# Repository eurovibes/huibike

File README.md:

<!-- SPDX-FileCopyrightText: 2023 Benedikt Spranger <bene@eurovibes.org> -->
<!-- SPDX-License-Identifier: CERN-OHL-S-2.0 -->

# huibike - Bike magnet sensor adaption board

## License rules

huibike is provided under the terms of the CERN-OHL-S license version 2 as
provided in the LICENSES/CERN-OHL-S-2.0 file.

Instead of adding license boilerplates to the individual files, huibike uses
SPDX license identifiers, which are machine parseable and considered legaly
equivalent.

The SPDX license identifier in huibike shall be added at the first possible
line in a file which can contain a comment. This is normally the first line
except for scripts. Scripts require the #!PATH_TO_INTERPRETER tag in the
first line; place the SPDX identifier into the second line.

The SPDX license identifier is added in form of a comment.

## Copyright and License

Copyright Benedikt Spranger 2021.
This source describes Open Hardware and is licensed under the CERNOHL-S v2.
You may redistribute and modify this source and make products using it
under the terms of the CERN-OHL-S v2
(https://ohwr.org/cern ohl s v2.txt ).
This source is distributed WITHOUT ANY EXPRESS OR IMPLIED
WARRANTY, INCLUDING OF MERCHANTABILITY, SATISFACTORY
QUALITY AND FITNESS FOR A PARTICULAR PURPOSE. Please see
the CERN-OHL-S v2 for applicable conditions.
Source location: https://github.com/eurovibes/huibike
As per CERN-OHL-S v2 section 4, should You produce hardware based
on this source, You must where practicable maintain the Source Location
visible on the external case of the huibike or other products you make using
this source.

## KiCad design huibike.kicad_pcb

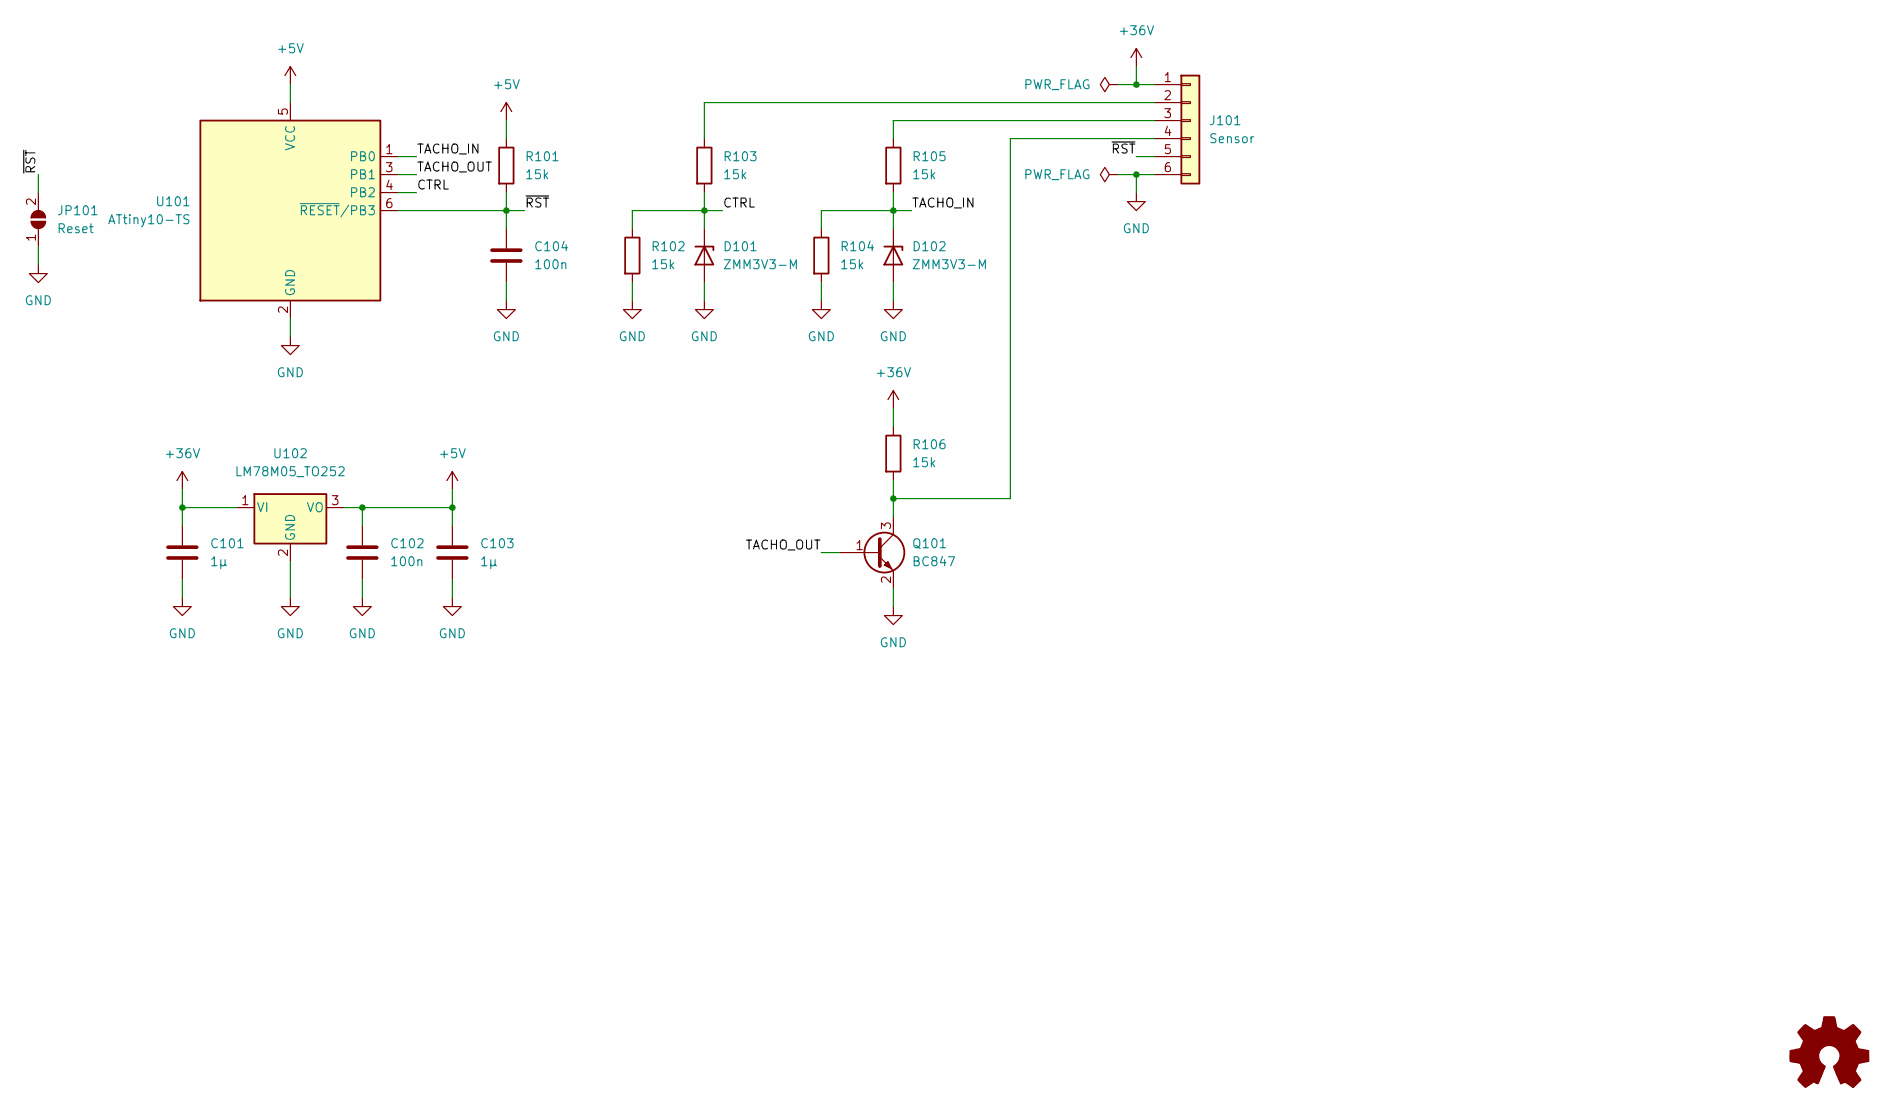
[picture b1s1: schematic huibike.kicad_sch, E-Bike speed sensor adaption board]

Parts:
C101, C103: 1µ; C_0805_2012Metric; LCSC# C28323
C102, C104: 100n; C_0402_1005Metric; LCSC# C1525
D101, D102: ZMM3V3-M; D_MiniMELF; LCSC# C8056
J101: Sensor; PinHeader_1x06_P2.54mm_Vertical
JP101: Reset; SolderJumper-2_P1.3mm_Open_Pad1.0x1.5mm
Q101: BC847; SOT-23; LCSC# C475630
R101, R102, R103, R104, R105, R106: 15k; R_0402_1005Metric; LCSC# C25756
U101: ATtiny10-TS; SOT-23-6; LCSC# C128438
U102: LM78M05_TO252; TO-252-2; LCSC# C58069

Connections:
+5V: C102.1, C103.1, R101.1, U101.5 (VCC), U102.3 (VO)
+36V: C101.1, J101.1, R106.1, U102.1 (VI)
/CTRL: D101.1 (K), R102.1, R103.2, U101.4 (PB2)
/TACHO_IN: D102.1 (K), R104.1, R105.2, U101.1 (PB0)
/TACHO_OUT: Q101.1 (B), U101.3 (PB1)
/~RST: C104.1, J101.5, JP101.2 (B), R101.2, U101.6 (~RESET/PB3)
GND: C101.2, C102.2, C103.2, C104.2, D101.2 (A), D102.2 (A), J101.6, JP101.1 (A), Q101.2 (E), R102.2, R104.2, U101.2 (GND), U102.2 (GND)
unnamed: J101.2, R103.1
unnamed: J101.3, R105.1
unnamed: J101.4, Q101.3 (C), R106.2

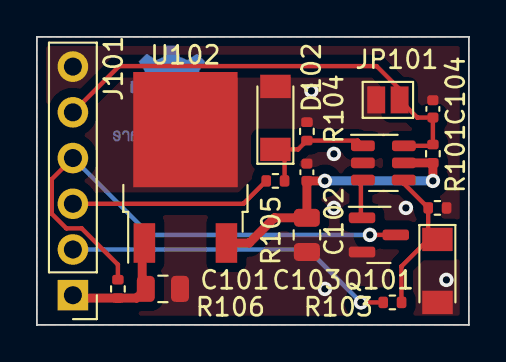
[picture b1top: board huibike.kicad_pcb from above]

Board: 2 copper layers, 24.0 x 16.0 mm, 17 parts (0 on the bottom side), 10 nets.

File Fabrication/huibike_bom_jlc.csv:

"Comment","Designator","Footprint","LCSC Part #"
"100n","C102,C104","C_0402_1005Metric","C1525"
"1µ","C101,C103","C_0805_2012Metric","C28323"
"ZMM3V3-M","D101,D102","D_MiniMELF","C8056"
"BC847","Q101","SOT-23","C475630"
"15k","R101,R102,R103,R104,R105,R106","R_0402_1005Metric","C25756"
"ATtiny10-TS","U101","SOT-23-6","C128438"
"LM78M05_TO252","U102","TO-252-2","C58069"

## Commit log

2023-05-03 Initial
2023-05-03 Add firmware
2023-05-03 Add README
2023-05-03 trigger commit
2023-05-04 Deploying to gh-pages from @ eurovibes/huibike@47f1ac4b527e57a29aed98668ab503cf53c90ca0 🚀
2023-05-04 Initial gh-pages commit
2023-05-06 Update Parts
2023-05-06 Deploying to gh-pages from @ eurovibes/huibike@27b0568947115e0d296c15c50f3c558930dfdfed 🚀

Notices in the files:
huibike.kicad_sch:
This work is licensed under the CERN-OHL-S v2
